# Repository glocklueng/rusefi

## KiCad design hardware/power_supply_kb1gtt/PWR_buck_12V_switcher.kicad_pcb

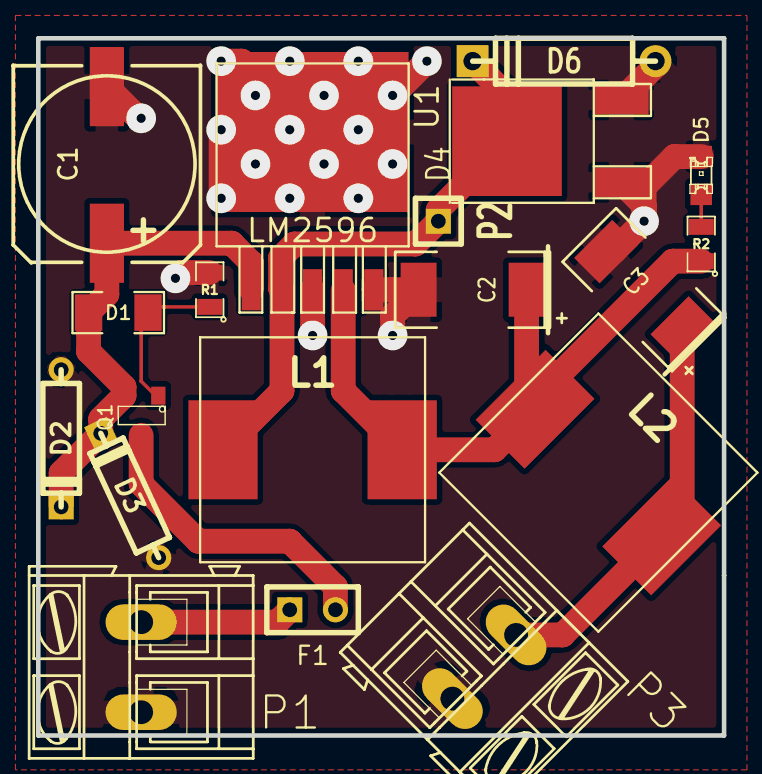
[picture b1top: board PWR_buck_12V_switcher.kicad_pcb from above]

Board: 2 copper layers, 38.1 x 38.7 mm, 19 parts (0 on the bottom side), 9 nets.

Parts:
C1: 470uF 25V; SMDSVP10
C2, C3: 220uF 16V; SM2512
D1: ZENERSMALL; SM1206
D2, D3: TVS; D3
D4: SCHDPAK; DPAK2
D5: GREEN; LED-0805
D6: DIODESCH; D4
F1: 3.5A; SIL-2
L1, L2: 38uH; SM100uH
P1, P3: CONN_2; AK300-2
P2: CONN_1; SIL-1
Q1: MOS_PRO; SOT23
R1, R2: 1k; SM0805
U1: LM2596; DPAK5

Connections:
/5V-REG: C3.1, L2.2, P3.1
/FB: C2.1, L1.2, L2.1, R2.1, U1.4
/OUT: D4.2, D6.2, L1.1, P2.1, U1.2
/VBAT: C1.1, D1.2, D2.2, D3.2, Q1.2, U1.1
/Vf: F1.2, Q1.3
/Vin: F1.1, P1.2
GND: C1.2, C2.2, C3.2, D2.1, D3.1, D4.1, D4.3, D5.2, D6.1, P1.1, P3.2, R1.2, U1.3, U1.5
unnamed: D1.1, Q1.1, R1.1
unnamed: D5.1, R2.2

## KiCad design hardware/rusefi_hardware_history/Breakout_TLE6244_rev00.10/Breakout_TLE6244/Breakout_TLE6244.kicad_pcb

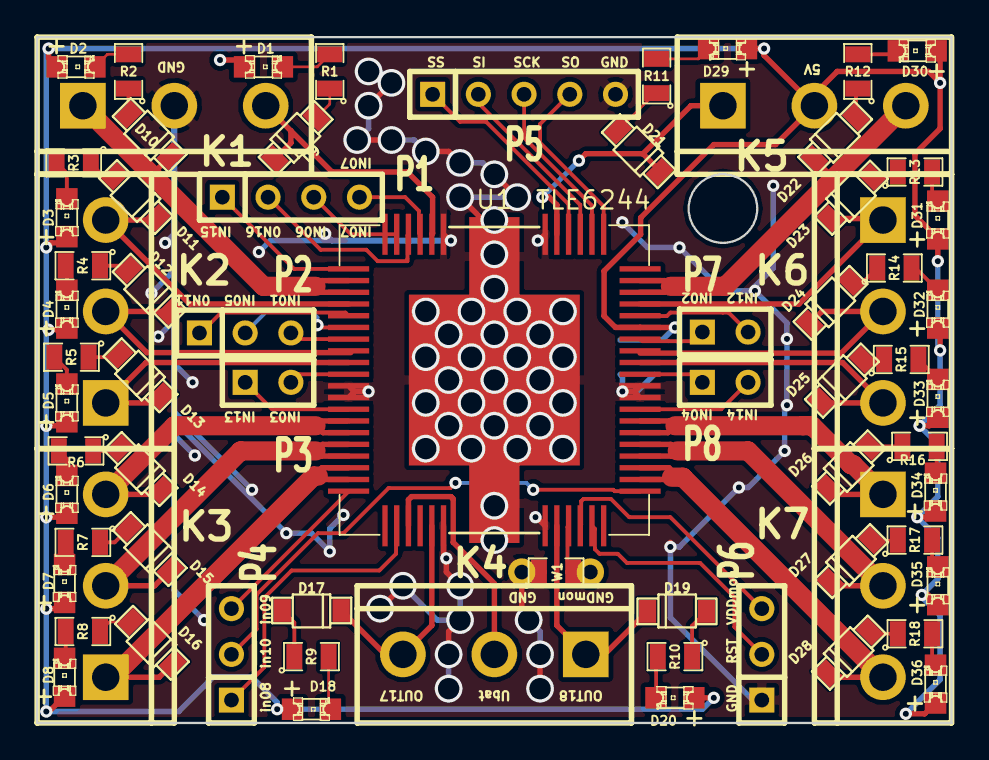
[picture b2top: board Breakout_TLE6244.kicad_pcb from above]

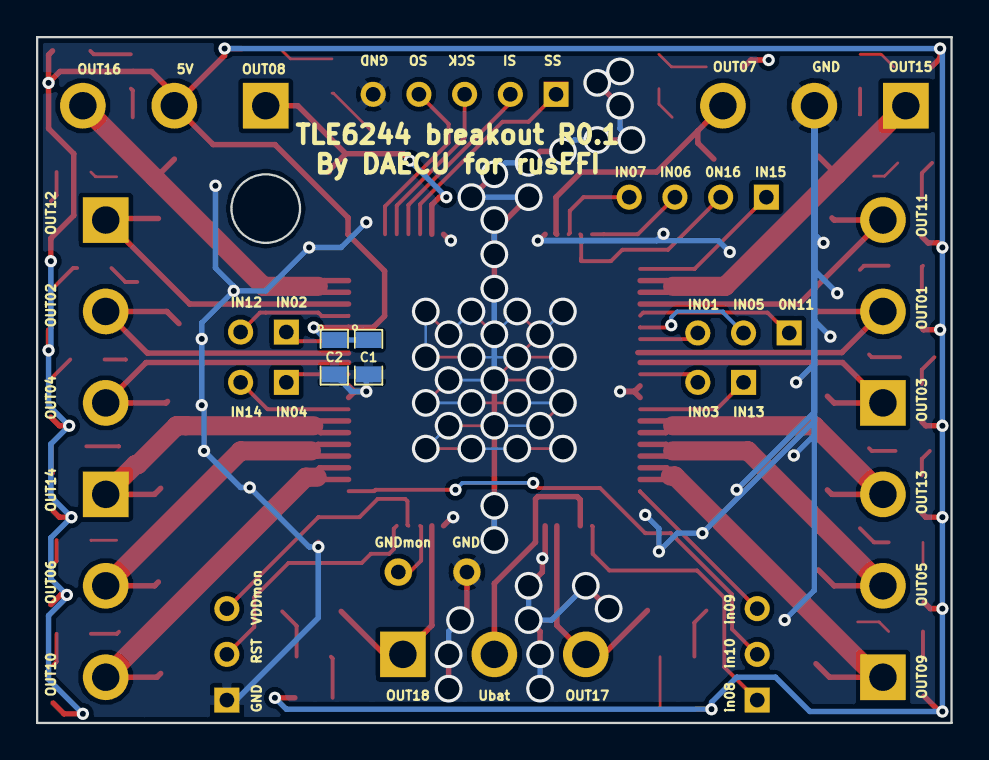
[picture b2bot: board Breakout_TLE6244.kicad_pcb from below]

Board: 4 copper layers, 50.8 x 38.1 mm, 73 parts (2 on the bottom side), 80 nets.

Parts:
C1: 1uF; SM0805
C2: .01uF; SM0805
D1, D2, D3, D4, D5, D6, D7, D8, D18, D20, D29, D30, D31, D32, D33, D34, D35, D36: LED-red; LED-0805_A
D9, D10, D11, D12, D13, D14, D15, D16, D17, D19, D21, D22, D23, D24, D25, D26, D27, D28: DIODE; SOD-123
K1, K2, K3, K4, K5, K6, K7: CONN_3; bornier3
P1: CONN_4; SIL-4
P2, P4, P6: CONN_3; SIL-3
P3, P7, P8: CONN_2; SIL-2
P5: CONN_5; SIL-5
R1, R2, R3, R4, R5, R6, R7, R8, R9, R10, R11, R12, R13, R14, R15, R16, R17, R18: 1K; SM0805
U1: TLE6244; HiQUAD64
W1: TEST; SM0805_jumper

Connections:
/5v: C1.1, C2.1, D1.1, D2.1, D3.1, D4.1, D5.1, D6.1, D7.1, D8.1, D18.1, D20.1, D29.1, D30.1, D31.1, D32.1, D33.1, D34.1, D35.1, D36.1, K5.2, U1.47
/GNDmon: U1.29, W1.2
/RST: P6.2, U1.31
/SCK: P5.3, U1.54
/SI: P5.2, U1.55
/SO: P5.4, U1.53
/SS: P5.1, U1.56
/Ubatt: K4.2, U1.23
/VDDmon: P6.3, U1.30
/in01: P2.3, U1.7
/in02: P7.1, U1.46
/in03: P3.2, U1.10
/in04: P8.1, U1.43
/in05: P2.2, U1.6
/in06: P1.3, U1.63, U1.64
/in07: P1.4, U1.61
/in08: P4.1, U1.22
/in09: P4.3, U1.20
/in10: P4.2, U1.33
/in11: P2.1, U1.5
/in12: P7.2, U1.48
/in13: P3.1, U1.13
/in14: P8.2, U1.40
/in15: P1.1, U1.1
/in16: P1.2, U1.62
/out01: D12.2, K2.2, U1.8
/out02: D24.2, K6.2, U1.45
/out03: D13.2, K2.1, U1.9
/out04: D25.2, K6.3, U1.44
/out05: D15.2, K3.2, U1.16, U1.17
/out06: D27.2, K7.2, U1.36, U1.37
/out07: D9.2, K1.3, U1.60
/out08: D21.2, K5.1, U1.57
/out09: D16.2, K3.1, U1.18, U1.19
/out10: D28.2, K7.3, U1.34, U1.35
/out11: D11.2, K2.3, U1.4
/out12: D23.2, K6.1, U1.49
/out13: D14.2, K3.3, U1.14, U1.15
/out14: D26.2, K7.1, U1.38, U1.39
/out15: D10.2, K1.1, U1.2, U1.3
/out16: D22.2, K5.3, U1.50, U1.51
/out17: D17.2, K4.3, U1.25
/out18: D19.2, K4.1, U1.28
GND: C1.2, C2.2, K1.2, P5.5, P6.1, U1.11, U1.12, U1.26, U1.27, U1.41, U1.42, U1.58, U1.59, U1.slug, W1.1
unnamed: D9.1, R1.1
unnamed: D21.1, R11.1
unnamed: D29.2, R11.2
unnamed: D1.2, R1.2
unnamed: D17.1, R9.1
unnamed: D18.2, R9.2
unnamed: D3.2, R3.2
unnamed: D11.1, R3.1
unnamed: D22.1, R12.1
unnamed: D30.2, R12.2
unnamed: D2.2, R2.2
unnamed: D10.1, R2.1
unnamed: D27.1, R17.1
unnamed: D28.1, R18.1
unnamed: D36.2, R18.2
unnamed: D35.2, R17.2
unnamed: D26.1, R16.1
unnamed: D34.2, R16.2
unnamed: D25.1, R15.1
unnamed: D33.2, R15.2
unnamed: D19.1, R10.1
unnamed: D20.2, R10.2
unnamed: D5.2, R5.2
unnamed: D7.2, R7.2
unnamed: D15.1, R7.1
unnamed: D14.1, R6.1
unnamed: D6.2, R6.2
unnamed: D13.1, R5.1
unnamed: D12.1, R4.1
unnamed: D4.2, R4.2
unnamed: D24.1, R14.1
unnamed: D32.2, R14.2
unnamed: D23.1, R13.1
unnamed: D31.2, R13.2
unnamed: D16.1, R8.1
unnamed: D8.2, R8.2

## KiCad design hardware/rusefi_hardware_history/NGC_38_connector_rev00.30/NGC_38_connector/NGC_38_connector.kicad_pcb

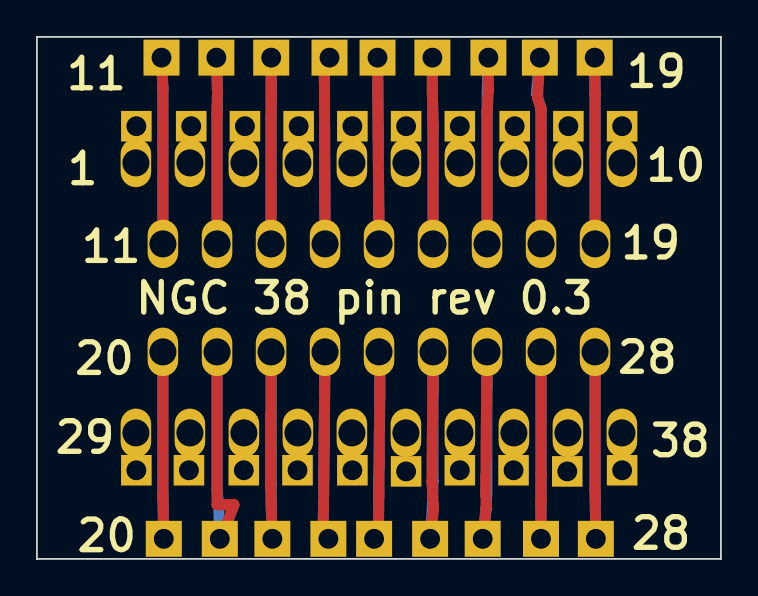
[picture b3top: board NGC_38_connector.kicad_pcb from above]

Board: 2 copper layers, 38.0 x 29.0 mm, 5 parts (0 on the bottom side), 38 nets.

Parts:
P1: DIL38; PCM_C1
P2, P4: CONN_10; SIL-10
P3, P5: CONN_9; SIL-9

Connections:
unnamed: P1.15, P3.5
unnamed: P1.10, P2.10
unnamed: P1.9, P2.9
unnamed: P1.8, P2.8
unnamed: P1.7, P2.7
unnamed: P1.6, P2.6
unnamed: P1.5, P2.5
unnamed: P1.4, P2.4
unnamed: P1.3, P2.3
unnamed: P1.2, P2.2
unnamed: P1.1, P2.1
unnamed: P1.19, P3.9
unnamed: P1.18, P3.8
unnamed: P1.17, P3.7
unnamed: P1.16, P3.6
unnamed: P1.20, P5.1
unnamed: P1.14, P3.4
unnamed: P1.13, P3.3
unnamed: P1.12, P3.2
unnamed: P1.11, P3.1
unnamed: P1.28, P5.9
unnamed: P1.27, P5.8
unnamed: P1.26, P5.7
unnamed: P1.25, P5.6
unnamed: P1.24, P5.5
unnamed: P1.23, P5.4
unnamed: P1.22, P5.3
unnamed: P1.21, P5.2
unnamed: P1.31, P4.3
unnamed: P1.34, P4.6
unnamed: P1.33, P4.5
unnamed: P1.32, P4.4
unnamed: P1.38, P4.10
unnamed: P1.30, P4.2
unnamed: P1.29, P4.1
unnamed: P1.37, P4.9
unnamed: P1.36, P4.8
unnamed: P1.35, P4.7

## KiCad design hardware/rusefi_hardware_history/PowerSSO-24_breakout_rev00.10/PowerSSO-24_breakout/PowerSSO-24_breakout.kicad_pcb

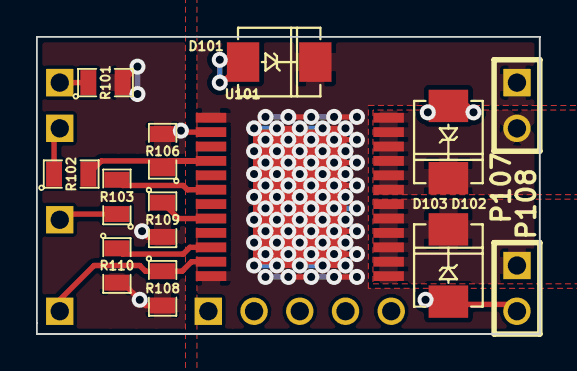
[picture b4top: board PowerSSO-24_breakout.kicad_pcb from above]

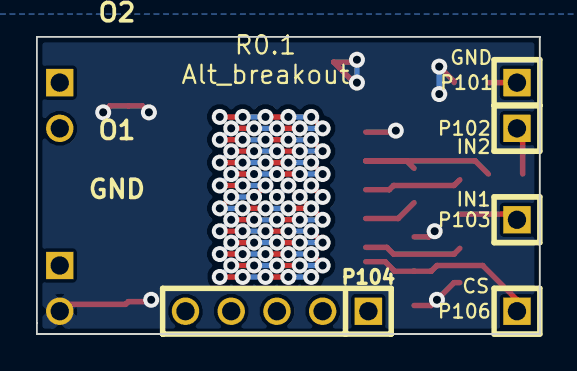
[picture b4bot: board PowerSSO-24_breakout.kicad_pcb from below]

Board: 2 copper layers, 27.9 x 16.5 mm, 18 parts (5 on the bottom side), 12 nets.

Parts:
D101, D102, D103: P6SMB36AT3G; DO-214AA(SMB)
P101, P102, P103, P106: CONN_1; SIL-1
P104: CONN_5; SIL-5
P107, P108: CONN_2; SIL-2
R101: TBD; SM0805
R102, R103, R106, R108: 10K; SM0805
R109, R110: 1K; SM0805
U101: VND5E025AKTR; PowerSSO-24

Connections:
/CS_DIS: P106.1, R108.1, U101.11
/I1: R109.1, U101.8
/I2: R110.1, U101.10
/IN1: R103.2, U101.6
/IN2: R102.2, R106.1, U101.4
/O1: D103.2, P108.1, U101.13, U101.14, U101.15, U101.16, U101.17, U101.18
/O2: D102.2, P107.2, U101.19, U101.20, U101.21, U101.22, U101.23, U101.24
/VCC: D101.2, P107.1, U101.1, U101.12, U101.EXP
GND: D101.1, D102.1, D103.1, P108.2, R101.2, R106.2, R108.2, R109.2, R110.2, U101.2
unnamed: P101.1, R101.1
unnamed: P103.1, R103.1
unnamed: P102.1, R102.1

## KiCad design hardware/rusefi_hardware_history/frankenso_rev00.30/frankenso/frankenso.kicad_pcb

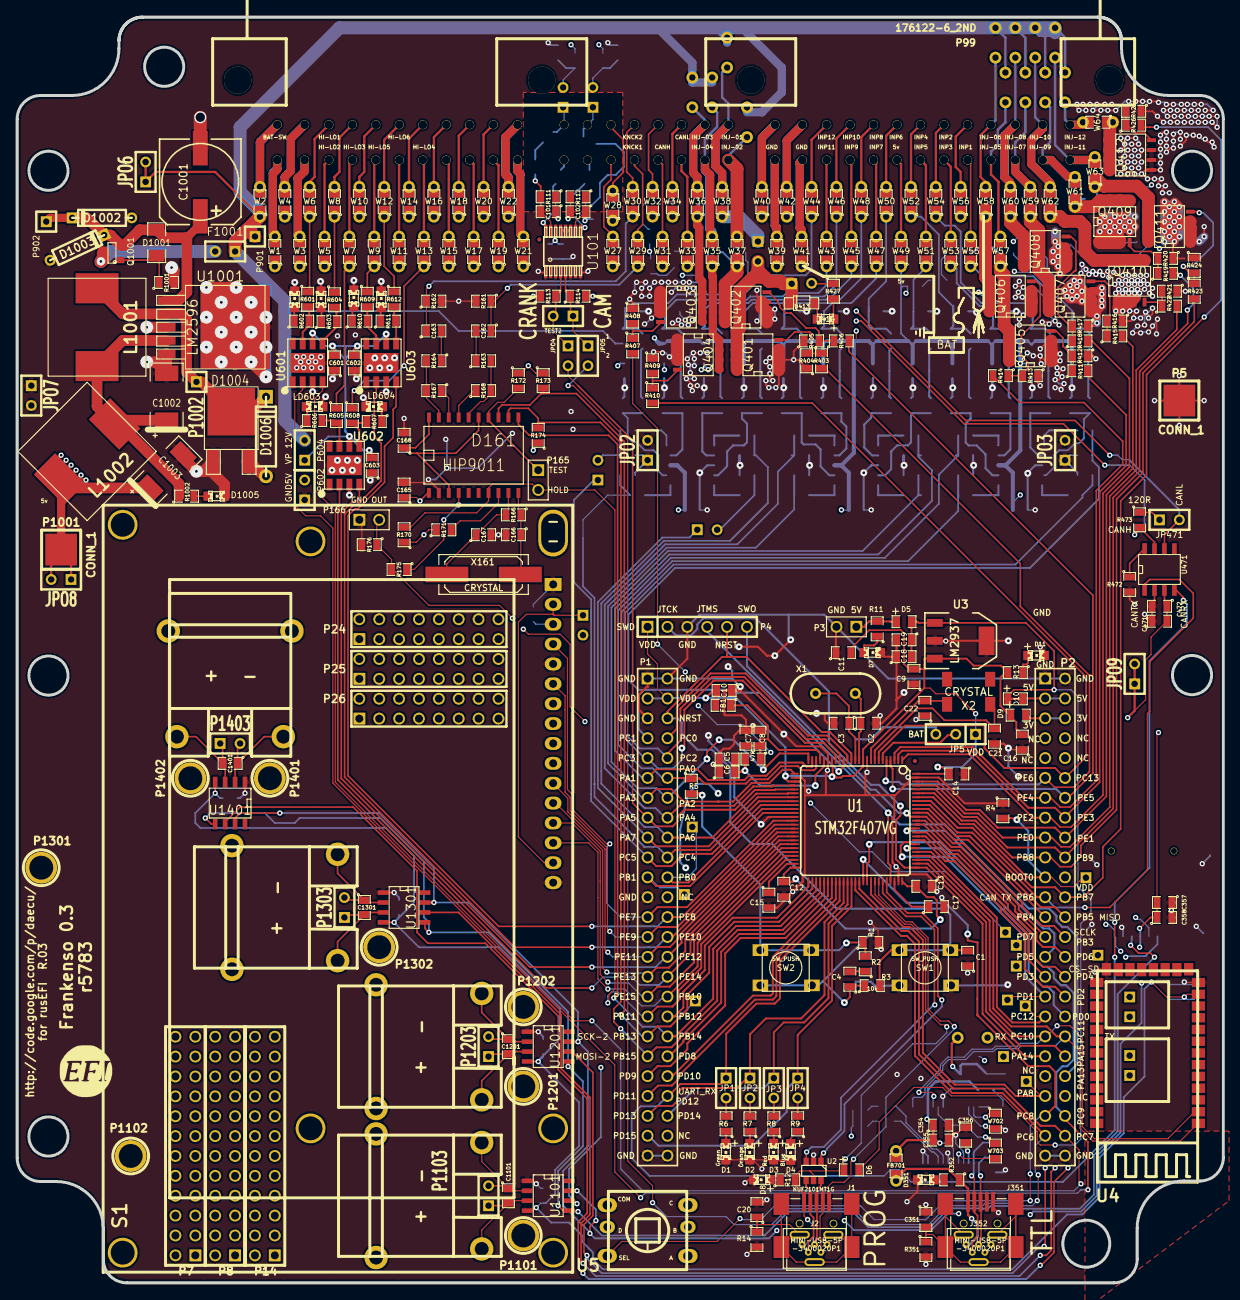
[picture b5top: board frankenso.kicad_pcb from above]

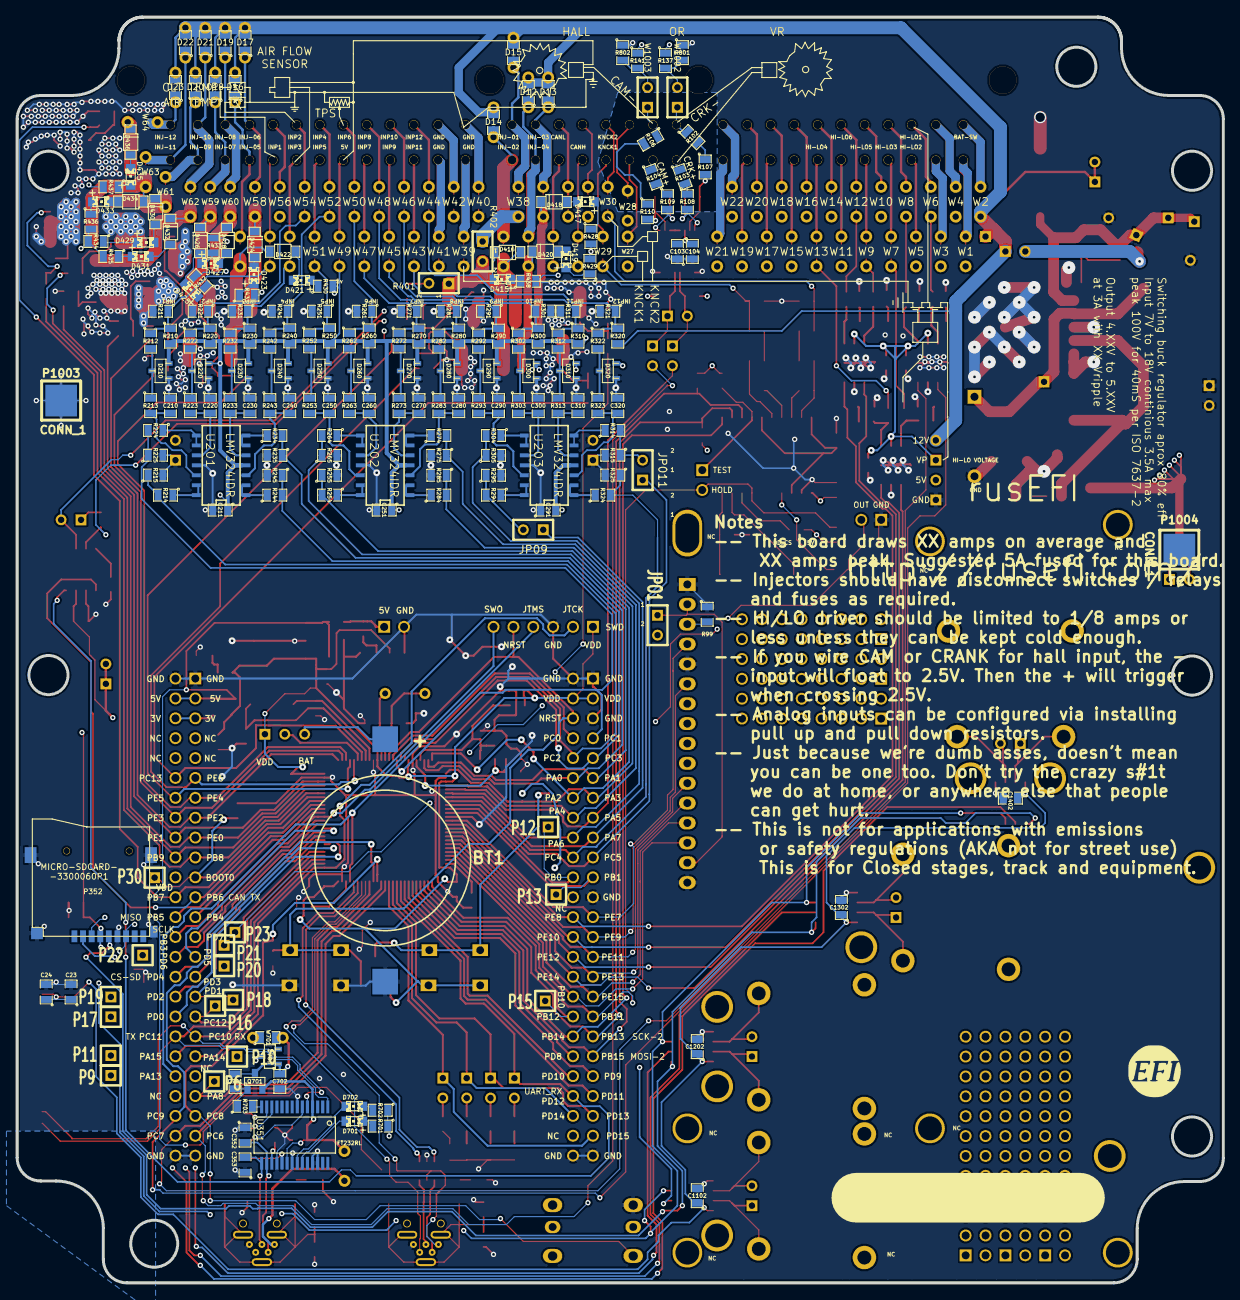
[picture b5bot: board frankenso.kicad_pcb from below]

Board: 4 copper layers, 154.1 x 161.7 mm, 516 parts (209 on the bottom side), 357 nets.

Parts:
BT1: BATTERY_CR2032; BATT_CR2032_MPD
C1, C5, C8, C210, C220, C230, C240, C250, C260, C270, C280, C290, C300, C310, C320: 0.01uF; SM0805
C2, C3, C166, C167: 20pF; SM0805
C4, C15, C17: 2u2F; SM0805
C6, C7, C16, C23: 1uF; SM0805
C9, C10, C11, C12, C13, C14, C18, C20, C24, C104, C165, C211, C251, C291, C355, C471, C601, C602, C603, C701, C702: 0.1uF; SM0805
C19, C354, C358, C472: 4.7uF; SM0805
C21, C22: 12.5pF; SM0805
C101, C102: 1000pF; SM0805
C103: 10uF; SM0805
C162, C163: .047uF; SM0805
C168: .022uF; SM0805
C351: 4700pF; SM0805
C352, C353: 47pF; SM0805
C356, C357: .1uF; SM0805
C1001: 470uF 25V; SMDSVP10
C1002, C1003: 220uF 16V; SM2512
C1101, C1201, C1301, C1401: 10nF; SM0805-SM0603
C1102, C1202, C1302, C1402: 100nF; SM0805-SM0603
D1, D7, D8, D11, D351, D701, D702: LED-grn; LED-0805_A
D2: LED-org; LED-0805_A
D3, D414, D415, D417, D419, D421, D423, D425, D427, D429, D431, D433, D435: LED-red; LED-0805_A
D4: LED-blu; LED-0805_A
D5, D6, D9, D10: DIODESCH; SM0805-diode
D12, D13, D14, D15, D16, D17, D18, D19, D20, D21, D22, D23: DIODESCH; SM0805_jumper
D161: HIP9011; SO20L
D210, D220, D230, D240, D250, D260, D270, D280, D290, D300, D310, D320, D703: DOUBLE_SCHOTTKY; sot23
D413, D416, D418, D420, D422, D424, D426, D428, D430, D432, D434, D436: DIODE; SOD-123
D1001: ZENERSMALL; SM1206
D1002, D1003: TVS; D3
D1004: SCHDPAK; DPAK2
D1005: LED-grn; LED-0805
D1006: DIODESCH; D4
F1001: 3.5A; SIL-2
FB1: FILTER; SM0805
FB701: FILTER; SM0805_jumper
G1: LOGO; LOGO_F
G2: LOGO
J1, J351: MINI-USB-5P-3400020P1
J2, J352: MINI-USB-5P-3400020P1V; MINI-USB_RCTP_V-T_B
JP1, JP2, JP3, JP4, JP471: JUMPER; JUMPER-2
JP5: JUMPER3; SIL-3
JP09, JP011: TEST-AN; SIL-2
JPO1: TEST-LCD; SIL-2
JPO2, JPO3, JPO6, JPO7, JPO8, JPO9: TEST-gnd; SIL-2
JPO4: TEST-CRK; SIL-2
JPO5: TEST-CAM; SIL-2
L1001, L1002: 38uH; SM100uH
LD601, LD602, LD603, LD604, LD605, LD606: LED-blu; LED-0805
P1, P2: CONN_25X2; PIN_ARRAY_25x2_A
P3: CONN_2; PIN_ARRAY_2_A
P4: CONN_6; PIN_ARRAY-6X1
P5, P1001, P1003, P1004: CONN_1; 1PIN_SMD
P6, P9, P10, P11, P12, P13, P15, P16, P17, P18, P19, P20, P21, P22, P23, P30, P901, P902, P1002: CONN_1; SIL-1
P7, P8, P14: CONN_12X2; pin_array_12x2
P24, P25, P26: CONN_8X2; pin_array_8x2
P99: 176122-6_2ND; 176122-6_2nd
P165, P166: CONN_2; PIN_ARRAY_2X1
P352: MICRO-SDCARD-CONNECTOR-3300060P1
P602, P604, P1103, P1203, P1303, P1403: CONN_2; SIL-2
P1101, P1102, P1201, P1202, P1301, P1302, P1401, P1402: CONN_1; 1pin
P1104, P1204, P1304, P1404: CONN_2; tcpl_PCC-SMP
Q401, Q402, Q403, Q404, Q405, Q406, Q407, Q408, Q409, Q410, Q411, Q412: OVP_DRIVER; SO8E_ST
Q701, Q1001: MOS_PRO; SOT23
R1, R3, R4, R113, R114, R163, R164, R175, R176, R212, R222, R232, R242, R252, R262, R272, R282, R292, R302, R312, R321, R322, R472: 10k; SM0805
R2: 100R; SM0805
R5: 330R; SM0805
R6, R7, R8, R9: 680R; SM0805
R10: 47R; SM0805
R11, R12, R13, R352, R701, R702, R703, R1001, R1002: 1k; SM0805
R14: 100k; SM0805
R99: 2K; SM0805
R102, R103, R104, R106, R107, R108, R109, R110, R111, R112: 5k; SM0805
R137, R141, R170, R171, R172, R173, R174, R404, R405, R408, R409, R412, R413, R416, R417, R420, R421, R424, R425, R427, R428, R429, R430, R431, R432, R433, R434, R435, R436, R437, R438: 1K; SM0805
R161, R162, R166, R351: 1M; SM0805
R167, R168: 68k; SM0805
R210, R220, R230, R240, R250, R260, R270, R280, R290, R300, R310, R602, R603, R606, R607, R610, R611: 2700; SM0805
R211, R221, R231, R241, R251, R261, R271, R281, R291, R301, R311: 500K; SM0805
R213, R223, R233, R243, R253, R263, R273, R283, R293, R303, R313, R323, R601, R604, R605, R608, R609, R612: 100; SM0805
R214, R215, R224, R225, R234, R235, R244, R245, R254, R255, R264, R265, R274, R275, R284, R285, R294, R295, R304, R305, R314, R315, R324, R325: 1500; SM0805
R320: 39k; SM0805
R401: OPT; SIL-2
R402: 0R; SIL-2
R403, R406, R407, R410, R411, R414, R415, R418, R419, R422, R423, R426: 20R; SM0805
R473: 120; SM0805
R801, R802: 0R; SM0805
S1: DISPLAY_BL; DISPLAY_4x20_BL
SW1, SW2: SW_PUSH; TL-1105
TEST2: TEST-C-C; SIL-2
U1: STM32F407VG; TQFP_100
U2: NUF2101MT1G; SOT-457
U3: LM2937; SOT223
U4: ITEAD_HC-0X; ITEAD_HC-05
U5: SKQUCAA010
U101: MAX9926/9927; maxim-10-QSOP16
U201, U202, U203: LMV324IDR; SO14N
U351: FT232RL; ssop-28
U471: SN65HVD230; SO8E
U601, U602, U603: TC4427; SOIC8-DFN
U1001: LM2596; DPAK5
U1101, U1201, U1301, U1401: MAX31855KASA; SO8E
W1, W2, W3, W4, W5, W6, W7, W8, W9, W10, W11, W12, W13, W14, W15, W16, W17, W18, W19, W20, W21, W22, W27, W28, W29, W30, W31, W32, W33, W34, W35, W36, W37, W38, W39, W40, W41, W42, W43, W44, W45, W46, W47, W48, W49, W50, W51, W52, W53, W54, W55, W56, W57, W58, W59, W60, W61, W62, W63, W64, W701: TEST; SM0805_jumper
W702, W703: TEST; SM0805
W1002, W1003: JMP; SIL-2
X1: CRYSTAL; HC-49V
X2: CRYSTAL; MC-306
X161: CRYSTAL; Q_49U3HMS

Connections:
/DD_HIP9011/5V: C18.2, C19.1, C103.2, C104.1, C165.1, C211.1, C251.1, C291.2, C1003.1, D5.2, D6.2, D10.1, D10.2, D161.1, D210.3, D220.3, D230.3, D240.3, D250.3, D260.3, D270.3, D280.3, D290.3, D300.3, D310.3, D320.3, D703.2, JPO1.2, JPO8.1, JPO8.2, L1002.2, P2.3, P2.4, P602.2, P1001.1, P1004.1, R113.1, R114.2, R137.1, R141.1, R170.1, R171.1, R172.1, R173.1, R174.1, R210.2, R220.2, R230.2, R240.2, R250.2, R260.2, R270.2, R280.2, R290.2, R300.2, R310.2, R401.2, R427.1, R428.2, R429.2, R430.2, R431.2, R432.2, R433.2, R434.2, R435.2, R436.2, R437.2, R438.2, R701.1, R702.1, U3.1, U101.14, U201.4, U202.4, U203.4, W49.1, W701.1
/DD_HIP9011/CS: D161.8, R171.2
/DD_HIP9011/INT/HLD: D161.7, P1.35, P165.2, R170.2, U1.48
/DD_HIP9011/INTOUT: D161.4, R175.1
/DD_HIP9011/KNOCK1: C162.1, R161.1, W29.1
/DD_HIP9011/KNOCK2: C163.1, R162.1, W30.1
/DD_HIP9011/OUT: P1.8, P166.2, R175.2, R176.1, U1.15
/DD_HIP9011/TEST: D161.14, P165.1, R172.2
/HD44780_VCC: JPO1.1, S1.2, S1.A
/PWR_buck_12V_switcher/FB: C1002.1, L1001.2, L1002.1, R1002.1, U1001.4
/PWR_buck_12V_switcher/OUT: D1004.2, D1006.2, L1001.1, P1002.1, U1001.2
/PWR_buck_12V_switcher/VBAT: C1001.1, D1001.2, D1002.2, D1003.2, P902.1, Q1001.2, U1001.1
/PWR_buck_12V_switcher/Vf: F1001.2, Q1001.3
/adc_amp_divider/INP1: R210.1, R211.1, R212.1, W55.1
/adc_amp_divider/INP2: R220.1, R221.1, R222.1, W54.1
/adc_amp_divider/INP3: R230.1, R231.1, R232.1, W53.1
/adc_amp_divider/INP4: R240.1, R241.1, R242.1, W52.1
/adc_amp_divider/INP5: R250.1, R251.1, R252.1, W51.1
/adc_amp_divider/INP6: R260.1, R261.1, R262.1, W50.1
/adc_amp_divider/INP7: R270.1, R271.1, R272.1, W47.1
/adc_amp_divider/INP8: R280.1, R281.1, R282.1, W48.1
/adc_amp_divider/INP9: R290.1, R291.1, R292.1, W45.1
/adc_amp_divider/INP10: R300.1, R301.1, R302.1, W46.1
/adc_amp_divider/INP11: R310.1, R311.1, R312.1, W43.1
/adc_amp_divider/INP12: R320.1, R321.1, R322.1, W44.1
/adc_amp_divider/OUT1: P1.10, R214.2, R215.1, U1.17
/adc_amp_divider/OUT2: P1.7, R224.2, R225.1, U1.16
/adc_amp_divider/OUT3: P1.12, R5.1, R234.2, R235.1, U1.23
/adc_amp_divider/OUT4: P1.9, R244.2, R245.1, U1.18
/adc_amp_divider/OUT5: P1.14, R254.2, R255.1, U1.25
/adc_amp_divider/OUT6: P1.11, R264.2, R265.1, U1.24
/adc_amp_divider/OUT7: P1.16, R274.2, R275.1, U1.29
/adc_amp_divider/OUT8: P1.13, R284.2, R285.1, U1.26
/adc_amp_divider/OUT9: JP09.1, P1.17, U1.32
/adc_amp_divider/OUT10: P1.18, R304.2, R305.1, U1.31
/adc_amp_divider/OUT11: JP011.1, P1.19, U1.34
/adc_amp_divider/OUT12: P1.20, R324.2, R325.1, U1.33
/can_brd_1/3.3V: C23.1, C24.1, C357.2, C358.1, C471.2, C472.1, C1102.1, C1202.1, C1302.1, C1402.1, D9.2, JPO9.1, JPO9.2, P2.5, P2.6, P352.4, U4.12, U471.3, U1101.4, U1201.4, U1301.4, U1401.4
/can_brd_1/CANH: R473.2, U471.7, W33.1
/can_brd_1/CANL: JP471.2, U471.6, W34.1
/can_brd_1/CAN_RX: JP1.1, P1.44, U1.59, U471.4
/can_brd_1/CAN_TX: P2.23, U1.92, U471.1
/cps_vrs_io_1/CAM: JPO5.1, R114.1, TEST2.1, U101.5
/cps_vrs_io_1/CAM+: P99.24, R104.1
/cps_vrs_io_1/CAM-: P99.32, R106.1, W1003.1
/cps_vrs_io_1/CRANK: JPO4.1, R113.2, TEST2.2, U101.4
/cps_vrs_io_1/CRK2+: P99.23, R103.1
/cps_vrs_io_1/CRK2-: P99.31, R102.1, W1002.1
/hi-lo/12V: D12.2, D13.2, D14.2, D15.2, D16.2, D17.2, D18.2, D19.2, D20.2, D21.2, D22.2, D23.2, F1001.1, JPO6.1, JPO6.2, P604.2, P901.1, R320.2, W2.1
/hi-lo/HL1: R601.1, W6.1
/hi-lo/HL2: R604.1, W8.1
/hi-lo/HL3: R605.1, W7.1
/hi-lo/HL4: R608.1, W13.1
/hi-lo/HL5: R609.1, W9.1
/hi-lo/HL6: R612.1, W12.1
/hi-lo/H_IN1: P2.48, U1.64, U601.4
/hi-lo/H_IN2: P1.32, U1.45, U602.2
/hi-lo/H_IN3: P2.46, U1.66, U601.2
/hi-lo/H_IN4: P1.30, U1.43, U602.4
/hi-lo/H_IN5: P1.26, U1.39, U603.4
/hi-lo/H_IN6: P1.28, U1.41, U603.2
/hi-lo/VP: C601.2, C602.2, C603.2, P604.1, U601.6, U602.6, U603.6
/inj_12ch/INJ-01: D413.2, Q401.2, R401.1, R402.2
/inj_12ch/INJ-01_2: R402.1, W38.1
/inj_12ch/INJ-01_5V: P2.11, R403.2, U1.5
/inj_12ch/INJ-02: D416.2, Q402.2, W37.1
/inj_12ch/INJ-02_5V: P2.14, R406.2, U1.4
/inj_12ch/INJ-03: D418.2, Q403.2, W36.1
/inj_12ch/INJ-03_5V: P2.27, P23.1, R407.2, U1.88
/inj_12ch/INJ-04: D420.2, Q404.2, W35.1
/inj_12ch/INJ-04_5V: P2.12, R410.2, U1.7
/inj_12ch/INJ-05: D422.2, Q405.2, W57.1
/inj_12ch/INJ-05_5V: P2.16, R411.2, U1.2
/inj_12ch/INJ-06: D424.2, Q406.2, W58.1
/inj_12ch/INJ-06_5V: P2.13, R414.2, U1.3
/inj_12ch/INJ-07: D426.2, Q407.2, W59.1
/inj_12ch/INJ-07_5V: P2.18, R415.2, U1.98
/inj_12ch/INJ-08: D428.2, Q408.2, W60.1
/inj_12ch/INJ-08_5V: P2.15, R418.2, U1.1
/inj_12ch/INJ-09: D430.2, Q409.2, W61.1
/inj_12ch/INJ-09_5V: P2.20, R419.2, U1.96
/inj_12ch/INJ-10: D432.2, Q410.2, W62.1
/inj_12ch/INJ-10_5V: P2.17, R422.2, U1.97
/inj_12ch/INJ-11: D434.2, Q411.2, W63.1
/inj_12ch/INJ-11_5V: P2.19, R423.2, U1.95
/inj_12ch/INJ-12: D436.2, Q412.2, W64.1
/inj_12ch/INJ-12_5V: P2.24, R426.2, U1.93
/mmc_usb_1/CB2: U351.13, W702.1
/mmc_usb_1/CB4: U351.12, W702.2
/mmc_usb_1/CS_SD_MODULE: P2.32, P352.2, U1.85
/mmc_usb_1/D+: C353.2, J351.3, J352.3, U351.15
/mmc_usb_1/D-: C352.2, J351.2, J352.2, U351.16
/mmc_usb_1/FTVCC: C354.1, C355.2, FB701.2, Q701.2, U351.4, U351.20
/mmc_usb_1/PWREN#: R703.2, U351.14
/mmc_usb_1/RESET: U351.19, W703.2
/mmc_usb_1/RI: U351.6, W703.1
/mmc_usb_1/Vbus: FB701.1, J351.1, J352.1, R352.1
/mmc_usb_1/shield: C351.2, J351.6, J352.6, R351.1
/stm32f407_board/BOOT0: P2.21, P30.1, R4.2, U1.94
/stm32f407_board/D+: J1.3, J2.3, U2.6
/stm32f407_board/D-: J1.2, J2.2, U2.4
/stm32f407_board/NRST: C1.2, P1.6, P4.5, R3.2, SW1.1, U1.14
/stm32f407_board/PA5: JPO4.2, P1.15, U1.30
/stm32f407_board/PA9: D6.1, J1.1, J2.1, R12.2, U1.68, U2.5
/stm32f407_board/PA10: J1.4, J2.4, U1.69
/stm32f407_board/PA11: U1.70, U2.3
/stm32f407_board/PA12: U1.71, U2.1
/stm32f407_board/PA15: P2.40, P11.1, U1.77
/stm32f407_board/PB0: P1.22, P12.1, U1.35
/stm32f407_board/PB1: P1.21, P13.1, U1.36
/stm32f407_board/PB3: P2.28, P4.6, P352.5, U1.89, U1101.5, U1201.5, U1301.5, U1401.5
/stm32f407_board/PB5: P2.26, P352.3, U1.91
/stm32f407_board/PB10: P1.34, S1.14, U1.47
/stm32f407_board/PB13: D161.13, P1.37, R173.2, U1.52
/stm32f407_board/PB14: D161.11, P1.38, U1.53
/stm32f407_board/PB15: D161.12, P1.39, R174.2, U1.54
/stm32f407_board/PC6: JPO5.2, P2.47, U1.63
/stm32f407_board/PC8: P2.45, U1.65, U5.6
/stm32f407_board/PC10: P2.37, U1.78, U4.2, U351.5
/stm32f407_board/PC11: P2.38, U1.79, U4.1, U351.1
/stm32f407_board/PC12: P2.35, P16.1, U1.80
/stm32f407_board/PD0: P2.36, P17.1, U1.81
/stm32f407_board/PD1: P2.33, P18.1, U1.82
/stm32f407_board/PD2: P2.34, P19.1, U1.83
/stm32f407_board/PD3: P2.31, P20.1, U1.84
/stm32f407_board/PD5: P2.29, P21.1, U1.86
/stm32f407_board/PD6: P2.30, P22.1, U1.87
/stm32f407_board/PD8: P1.40, U1.55, U5.1
/stm32f407_board/PD9: P1.41, U1.56, U5.3
/stm32f407_board/PD10: P1.42, U1.57, U5.2
/stm32f407_board/PD11: P1.43, U1.58, U5.5
/stm32f407_board/PD13: JP2.1, P1.45, U1.60
/stm32f407_board/PD14: JP3.1, P1.46, U1.61
/stm32f407_board/PD15: JP4.1, P1.47, U1.62
/stm32f407_board/PE7: P1.25, S1.4, U1.38
/stm32f407_board/PE9: P1.27, S1.6, U1.40
/stm32f407_board/PE11: P1.29, S1.11, U1.42
/stm32f407_board/PE13: P1.31, S1.12, U1.44
/stm32f407_board/PE15: P1.33, S1.13, U1.46
/stm32f407_board/VDD: C4.1, C9.2, C10.2, C11.2, C12.2, C13.2, C14.2, C16.2, D9.1, FB1.2, JP5.1, P1.3, P1.4, P4.1, R3.1, R13.2, SW2.2, U1.11, U1.19, U1.28, U1.50, U1.75, U1.100, U3.3
/stm32f407_board/shield: C20.1, J1.6, J2.6, R14.1
/thermocouple1//CS: P1.36, P15.1, U1.51, U1101.6
/thermocouple1/MISO: P2.25, P352.7, U1.90, U1101.7, U1201.7, U1301.7, U1401.7
/thermocouple1/TCPL+: C1101.2, P1103.1, P1104.2, U1101.3
/thermocouple1/TCPL-: C1101.1, P1103.2, P1104.1, U1101.2
/thermocouple2//CS: P2.39, P4.2, P10.1, U1.76, U1201.6
/thermocouple2/TCPL+: C1201.2, P1203.1, P1204.2, U1201.3
/thermocouple2/TCPL-: C1201.1, P1203.2, P1204.1, U1201.2
/thermocouple3//CS: P2.43, P6.1, U1.67, U1301.6
/thermocouple3/TCPL+: C1301.2, P1303.1, P1304.2, U1301.3
/thermocouple3/TCPL-: C1301.1, P1303.2, P1304.1, U1301.2
/thermocouple4//CS: P2.42, P4.4, P9.1, U1.72, U1401.6
/thermocouple4/TCPL+: C1401.2, P1403.1, P1404.2, U1401.3
/thermocouple4/TCPL-: C1401.1, P1403.2, P1404.1, U1401.2
GND: BT1.2, C1.1, C2.2, C3.2, C5.1, C6.1, C7.1, C8.1, C9.1, C10.1, C11.1, C12.1, C13.1, C14.1, C15.2, C16.1, C17.2, C18.1, C19.2, C20.2, C21.1, C22.1, C23.2, C24.2, C103.1, C104.2, C165.2, C166.2, C167.2, C168.2, C210.1, C211.2, C220.1, C230.1, C240.1, C250.1, C251.2, C260.1, C270.1, C280.1, C290.1, C291.1, C300.1, C310.1, C320.1, C351.1, C352.1, C353.1, C354.2, C355.1, C356.1, C357.1, C358.2, C471.1, C472.2, C601.1, C602.1, C603.1, C702.2, C1001.2, C1002.2, C1003.2, C1102.2, C1202.2, C1302.2, C1402.2, D1.2, D2.2, D3.2, D4.2, D7.2, D8.2, D11.2, D161.2, D210.1, D220.1, D230.1, D240.1, D250.1, D260.1, D270.1, D280.1, D290.1, D300.1, D310.1, D320.1, D351.2, D1002.1, D1003.1, D1004.1, D1004.3, D1005.2, D1006.1, J1.5, J2.5, J351.5, J352.5, JPO2.1, JPO2.2, JPO3.1, JPO3.2, JPO7.1, JPO7.2, LD601.2, LD602.2, LD603.2, LD604.2, LD605.2, LD606.2, P1.1, P1.2, P1.5, P1.23, P1.49, P1.50, P2.1, P2.2, P2.49, P2.50, P3.2, P4.3, P5.1, P166.1, P352.6, P352.G1, P352.G2, P352.G3, P352.G4, P602.1, P1003.1, Q401.3, Q402.3, Q403.3, Q404.3, Q405.3, Q406.3, Q407.3, Q408.3, Q409.3, Q410.3, Q411.3, Q412.3, R1.2, R4.1, R14.2, R99.1, R161.2, R162.2, R176.2, R211.2, R215.2, R221.2, R225.2, R231.2, R235.2, R241.2, R245.2, R251.2, R255.2, R261.2, R265.2, R271.2, R275.2, R281.2, R285.2, R291.2, R295.2, R301.2, R305.2, R311.2, R315.2, R321.2, R325.2, R351.2, R404.1, R405.1, R408.1, R409.1, R412.1, R413.1, R416.1, R417.1, R420.1, R421.1, R424.1, R425.1, R472.2, R801.1, R802.1, R1001.2, S1.1, S1.5, S1.K, SW1.2, U1.10, U1.20, U1.27, U1.37, U1.74, U1.99, U2.2, U3.2, U3.4, U4.13, U4.21, U4.22, U5.4, U101.1, U101.3, U101.6, U101.8, U101.11, U101.12, U101.13, U201.11, U202.11, U203.11, U351.7, U351.18, U351.21, U351.25, U351.26, U471.2, U601.3, U601.9, U602.3, U602.9, U603.3, U603.9, U1001.3, U1001.5, U1101.1, U1201.1, U1301.1, U1401.1, W39.1, W40.1, W41.1, W42.1
unnamed: P99.12, W2.2
unnamed: P99.35, W32.2
unnamed: D12.1, P99.29, W35.2
unnamed: D15.1, P99.38, W38.2
unnamed: P99.28, W33.2
unnamed: D13.1, P99.37, W36.2
unnamed: P99.27, W31.2
unnamed: P99.36, W34.2
unnamed: P99.26, W29.2
unnamed: P99.25, W27.2
unnamed: P99.34, W30.2
unnamed: P99.33, W28.2
unnamed: D14.1, P99.30, W37.2
unnamed: D21.1, P99.63, W62.2
unnamed: D20.1, P99.50, W61.2
unnamed: D19.1, P99.62, W60.2
unnamed: D22.1, P99.51, W63.2
unnamed: D18.1, P99.49, W59.2
unnamed: D17.1, P99.61, W58.2
unnamed: D16.1, P99.48, W57.2
unnamed: P99.60, W56.2
unnamed: P99.47, W55.2
unnamed: R99.2, S1.3
unnamed: D23.1, P99.64, W64.2
unnamed: P99.40, W41.2
unnamed: P99.42, W45.2
unnamed: P99.54, W44.2
unnamed: P99.41, W43.2
unnamed: P99.53, W42.2
unnamed: P99.55, W46.2
unnamed: P99.52, W40.2
unnamed: P99.39, W39.2
unnamed: P99.59, W54.2
unnamed: P99.46, W53.2
unnamed: P99.58, W52.2
unnamed: P99.45, W51.2
unnamed: P99.57, W50.2
unnamed: P99.44, W49.2
unnamed: P99.56, W48.2
unnamed: P99.43, W47.2
unnamed: P99.19, W16.2
unnamed: P99.11, W21.2
unnamed: P99.22, W22.2
unnamed: P99.21, W20.2
unnamed: P99.18, W14.2
unnamed: P99.20, W18.2
unnamed: P99.10, W19.2
unnamed: P99.9, W17.2
unnamed: P99.8, W15.2
unnamed: P99.13, W4.2
unnamed: P99.2, W3.2
unnamed: P99.1, W1.2
unnamed: P99.3, W5.2
unnamed: P99.7, W13.2
unnamed: P99.17, W12.2
unnamed: P99.6, W11.2
unnamed: P99.16, W10.2
unnamed: P99.5, W9.2
unnamed: P99.15, W8.2
unnamed: P99.4, W7.2
unnamed: P99.14, W6.2
unnamed: D433.1, R436.1
unnamed: D433.2, D434.1
unnamed: D431.1, R435.1
unnamed: D431.2, D432.1
unnamed: D435.2, D436.1
unnamed: D435.1, R437.1
unnamed: D427.1, R433.1
unnamed: D425.2, D426.1
unnamed: D425.1, R432.1
unnamed: D427.2, D428.1
unnamed: D429.2, D430.1
unnamed: D429.1, R434.1
unnamed: Q402.1, R405.2, R406.1
unnamed: D414.1, R427.2
unnamed: D413.1, D414.2
unnamed: D417.1, R428.1
unnamed: D417.2, D418.1
unnamed: D419.2, D420.1
unnamed: D419.1, R429.1
unnamed: D421.2, D422.1
unnamed: D421.1, R430.1
unnamed: D423.2, D424.1
unnamed: D423.1, R431.1
unnamed: D415.2, D416.1
unnamed: D415.1, R438.1
unnamed: Q404.1, R409.2, R410.1
unnamed: Q405.1, R411.1, R412.2
unnamed: Q403.1, R407.1, R408.2
unnamed: Q401.1, R403.1, R404.2
unnamed: Q406.1, R413.2, R414.1
unnamed: Q412.1, R425.2, R426.1
unnamed: Q411.1, R423.1, R424.2
unnamed: Q410.1, R421.2, R422.1
unnamed: Q409.1, R419.1, R420.2
unnamed: Q408.1, R417.2, R418.1
unnamed: Q407.1, R415.1, R416.2
unnamed: JP011.2, R314.2, R315.1
unnamed: R304.1, U203.8, U203.9
unnamed: C290.2, R293.2, U203.12
unnamed: D320.2, R322.2, R323.1
unnamed: D310.2, R312.2, R313.1
unnamed: C320.2, R323.2, U203.3
unnamed: R224.1, U201.8, U201.9
unnamed: D280.2, R282.2, R283.1
unnamed: D270.2, R272.2, R273.1
unnamed: D290.2, R292.2, R293.1
unnamed: D300.2, R302.2, R303.1
unnamed: R264.1, U202.8, U202.9
unnamed: R274.1, U202.6, U202.7
unnamed: R284.1, U202.1, U202.2
unnamed: R254.1, U202.13, U202.14
unnamed: R244.1, U201.1, U201.2
unnamed: R234.1, U201.6, U201.7
unnamed: C230.2, R233.2, U201.5
unnamed: C310.2, R313.2, U203.5
unnamed: R314.1, U203.6, U203.7
unnamed: R324.1, U203.1, U203.2
unnamed: JP09.2, R294.2, R295.1
unnamed: C250.2, R253.2, U202.12
unnamed: C260.2, R263.2, U202.10
unnamed: C280.2, R283.2, U202.3
unnamed: R214.1, U201.13, U201.14
unnamed: D230.2, R232.2, R233.1
unnamed: C220.2, R223.2, U201.10
unnamed: C210.2, R213.2, U201.12
unnamed: C270.2, R273.2, U202.5
unnamed: C240.2, R243.2, U201.3
unnamed: R294.1, U203.13, U203.14
unnamed: C300.2, R303.2, U203.10
unnamed: D250.2, R252.2, R253.1
unnamed: D260.2, R262.2, R263.1
unnamed: D210.2, R212.2, R213.1
unnamed: D220.2, R222.2, R223.1
unnamed: D240.2, R242.2, R243.1
unnamed: C701.2, C702.1, D703.1, Q701.3, W701.2
unnamed: D701.2, U351.23
unnamed: D702.1, R702.2
unnamed: D702.2, U351.22
unnamed: D701.1, R701.2
unnamed: C701.1, Q701.1, R703.1
unnamed: D351.1, R352.2
unnamed: C356.2, U351.17
unnamed: R472.1, U471.8
unnamed: JP471.1, R473.1
unnamed: R104.2, R109.1
unnamed: R103.2, R108.1
unnamed: R102.2, R107.1
unnamed: C102.1, R110.2, R112.1, U101.10
unnamed: R106.2, R110.1
unnamed: C102.2, R109.2, R112.2, U101.9
unnamed: C101.2, R107.2, R111.2, U101.15
unnamed: C101.1, R108.2, R111.1, U101.16
unnamed: R137.2, R801.2, W1002.2
unnamed: R141.2, R802.2, W1003.2
unnamed: R601.2, R602.2, U601.7
unnamed: R603.2, R604.2, U601.5
unnamed: R605.2, R606.2, U602.7
unnamed: LD603.1, R606.1
unnamed: LD605.1, R610.1
unnamed: R609.2, R610.2, U603.7
unnamed: R611.2, R612.2, U603.5
unnamed: LD606.1, R611.1
unnamed: R607.2, R608.2, U602.5
unnamed: LD602.1, R603.1
unnamed: LD604.1, R607.1
unnamed: LD601.1, R602.1
unnamed: C163.2, R164.1
unnamed: D161.17, R168.1
unnamed: D161.16, R163.2, R168.2
unnamed: D161.19, R164.2, R167.2
unnamed: D161.18, R167.1
unnamed: C162.2, R163.1
unnamed: C168.1, D161.3, D161.15, D161.20
unnamed: C167.1, D161.9, R166.2, X161.1
unnamed: C166.1, D161.10, R166.1, X161.2
unnamed: D1001.1, Q1001.1, R1001.1
unnamed: D1005.1, R1002.2
unnamed: C22.2, U1.9, X2.1
unnamed: C21.2, U1.8, X2.2
unnamed: C2.1, U1.12, X1.2
unnamed: D1.1, R6.1
unnamed: D2.1, R7.1
unnamed: D3.1, R8.1
unnamed: D4.1, R9.1
unnamed: D7.1, R11.1
unnamed: D8.1, R12.1
unnamed: D11.1, R13.1
unnamed: D5.1, P3.1, R11.2
unnamed: BT1.1, JP5.3
unnamed: JP5.2, U1.6
unnamed: JP4.2, R9.2
unnamed: JP3.2, R8.2
unnamed: JP2.2, R7.2
unnamed: JP1.2, R6.2
unnamed: R1.1, R2.2, R5.2, SW2.1
unnamed: C5.2, C6.2, R10.2, U1.21
unnamed: C3.1, U1.13, X1.1
unnamed: C17.1, U1.73
unnamed: C15.1, U1.49
unnamed: C4.2, R2.1
unnamed: C7.2, C8.2, FB1.1, R10.1, U1.22
